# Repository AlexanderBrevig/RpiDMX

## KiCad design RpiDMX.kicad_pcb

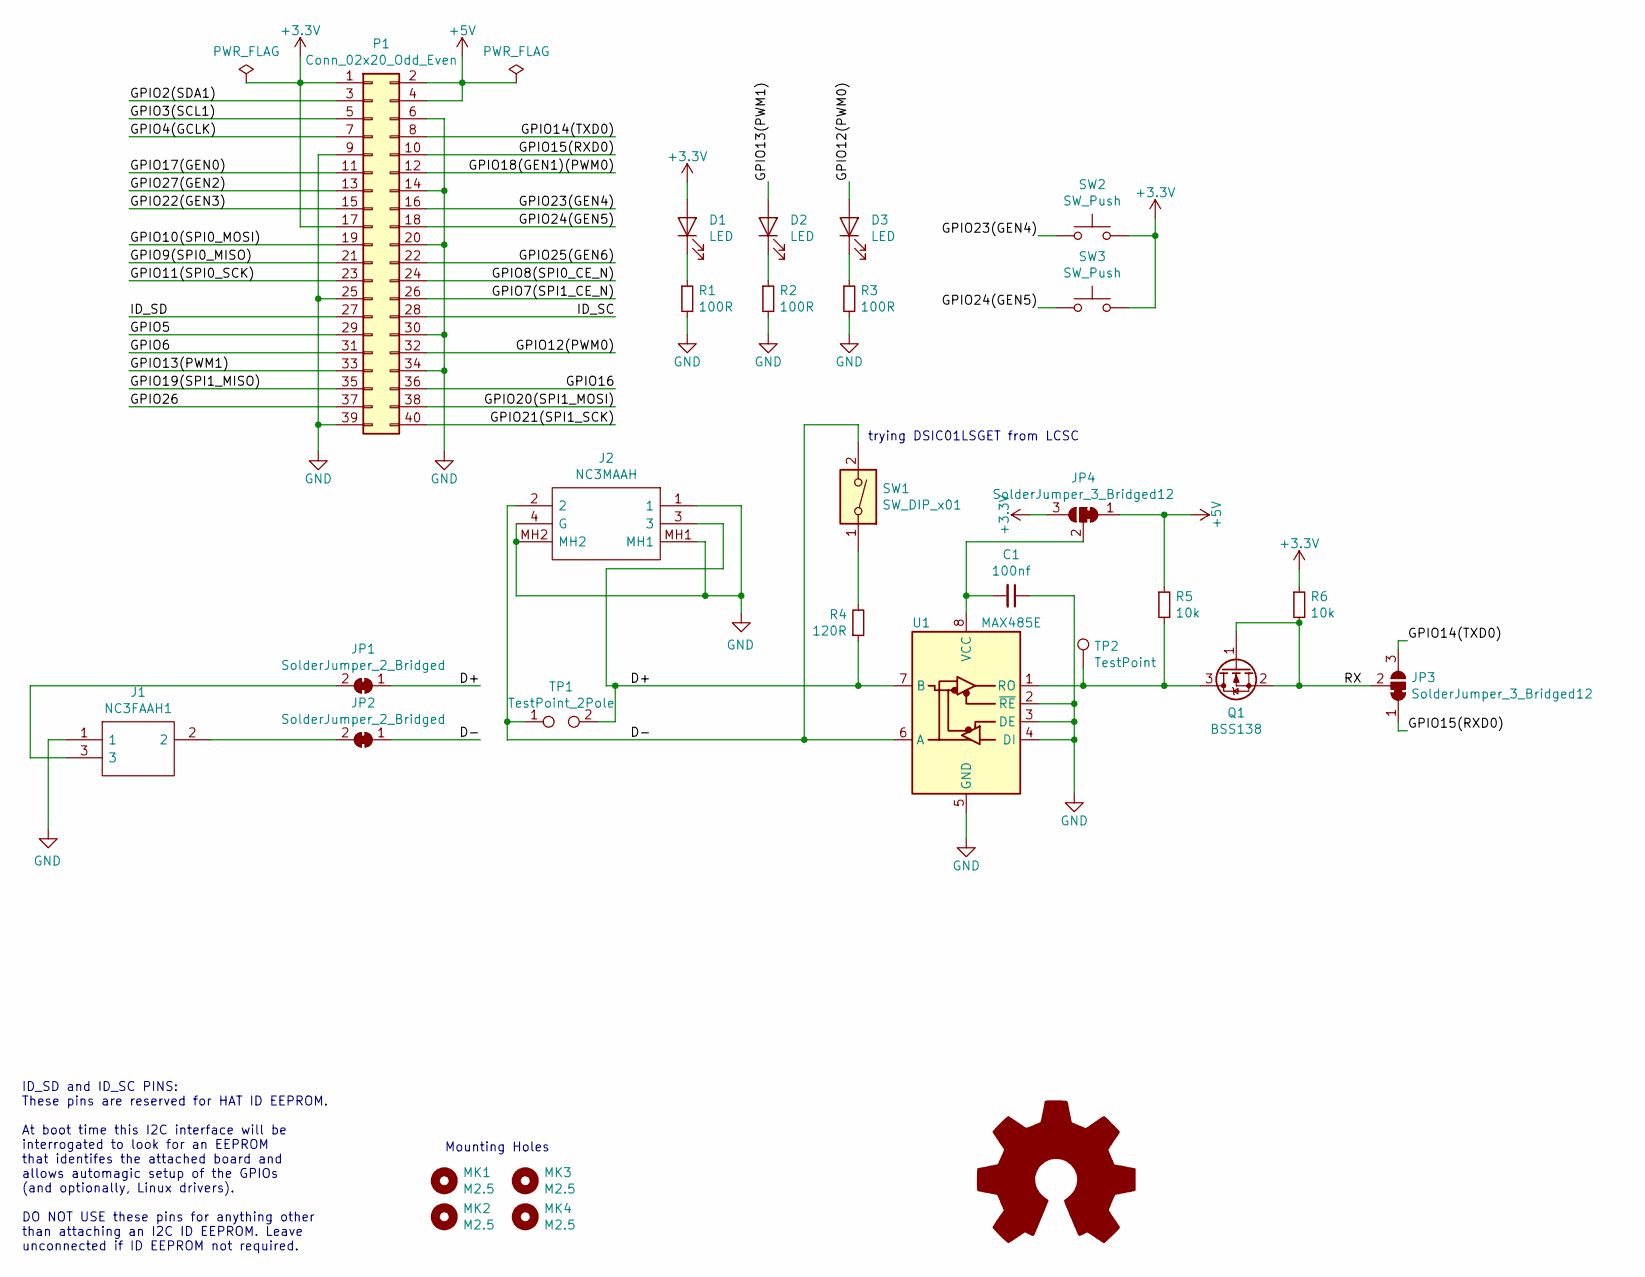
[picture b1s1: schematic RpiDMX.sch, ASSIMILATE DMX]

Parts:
C1: 100nf; C_0805_2012Metric_Pad1.15x1.40mm_HandSolder
D1, D2, D3: LED; LED_0805_2012Metric_Pad1.15x1.40mm_HandSolder
J1: NC3FAAH1; Mouser Part Number 568-NC3FAAH-1
J2: NC3MAAH; Mouser Part Number 568-NC3MAAH
JP1, JP2: SolderJumper_2_Bridged; SolderJumper-2_P1.3mm_Bridged_RoundedPad1.0x1.5mm
JP3, JP4: SolderJumper_3_Bridged12; SolderJumper-3_P1.3mm_Bridged12_RoundedPad1.0x1.5mm_NumberL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
MK1, MK2, MK3, MK4: M2.5; MountingHole_2.7mm_M2.5
P1: Conn_02x20_Odd_Even; PinSocket_2x20_P2.54mm_Vertical
Q1: BSS138; SOT-23
R1, R2, R3: 100R; R_0805_2012Metric_Pad1.15x1.40mm_HandSolder
R4: 120R; R_0805_2012Metric_Pad1.15x1.40mm_HandSolder
R5, R6: 10k; R_0805_2012Metric_Pad1.15x1.40mm_HandSolder
SW1: SW_DIP_x01; SW_DIP_SPSTx01_Slide_Omron_A6S-110x_W8.9mm_P2.54mm
SW2, SW3: SW_Push; SW_SPST_B3U-1000P
TP1: TestPoint_2Pole; TestPoint_2Pads_Pitch2.54mm_Drill0.8mm
TP2: TestPoint; TestPoint_THTPad_D1.5mm_Drill0.7mm
U1: MAX485E; SOIC-8_3.9x4.9mm_P1.27mm

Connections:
+3V3: D1.2 (A), JP4.3 (B), P1.1, P1.17, R6.1, SW2.2, SW3.2
+5V: JP4.1 (A), P1.2, P1.4, R5.1
/D+: J2.3, JP1.1 (A), R4.1, TP1.2, U1.7 (B)
/D-: J2.2, JP2.1 (A), SW1.2, TP1.1, U1.6 (A)
/GPIO2(SDA1): P1.3
/GPIO3(SCL1): P1.5
/GPIO4(GCLK): P1.7
/GPIO5: P1.29
/GPIO6: P1.31
/GPIO7(SPI1_CE_N): P1.26
/GPIO8(SPI0_CE_N): P1.24
/GPIO9(SPI0_MISO): P1.21
/GPIO10(SPI0_MOSI): P1.19
/GPIO11(SPI0_SCK): P1.23
/GPIO12(PWM0): D3.2 (A), P1.32
/GPIO13(PWM1): D2.2 (A), P1.33
/GPIO14(TXD0): JP3.3 (B), P1.8
/GPIO15(RXD0): JP3.1 (A), P1.10
/GPIO16: P1.36
/GPIO17(GEN0): P1.11
/GPIO18(GEN1)(PWM0): P1.12
/GPIO19(SPI1_MISO): P1.35
/GPIO20(SPI1_MOSI): P1.38
/GPIO21(SPI1_SCK): P1.40
/GPIO22(GEN3): P1.15
/GPIO23(GEN4): P1.16, SW2.1
/GPIO24(GEN5): P1.18, SW3.1
/GPIO25(GEN6): P1.22
/GPIO26: P1.37
/GPIO27(GEN2): P1.13
/ID_SC: P1.28
/ID_SD: P1.27
/RX: JP3.2 (C), Q1.1 (G), Q1.2 (S), R6.2
GND: C1.1, J1.1, J2.1, J2.4 (G), J2.MH1, J2.MH2, P1.6, P1.9, P1.14, P1.20, P1.25, P1.30, P1.34, P1.39, R1.2, R2.2, R3.2, U1.2 (~RE), U1.3 (DE), U1.4 (DI), U1.5 (GND)
unnamed: C1.2, JP4.2 (C), U1.8 (VCC)
unnamed: D1.1 (K), R1.1
unnamed: D2.1 (K), R2.1
unnamed: D3.1 (K), R3.1
unnamed: J1.2, JP2.2 (B)
unnamed: J1.3, JP1.2 (B)
unnamed: Q1.3 (D), R5.2, TP2.1, U1.1 (RO)
unnamed: R4.2, SW1.1

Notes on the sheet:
ID_SD and ID_SC PINS: These pins are reserved for HAT ID EEPROM. At boot time this I2C interface will be interrogated to look for an EEPROM that identifes the attached board and allows automagic setup of the GPIOs (and optionally, Linux drivers). DO NOT USE these pins for anything other than attach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
Mounting Holes
trying DSIC01LSGET from LCSC

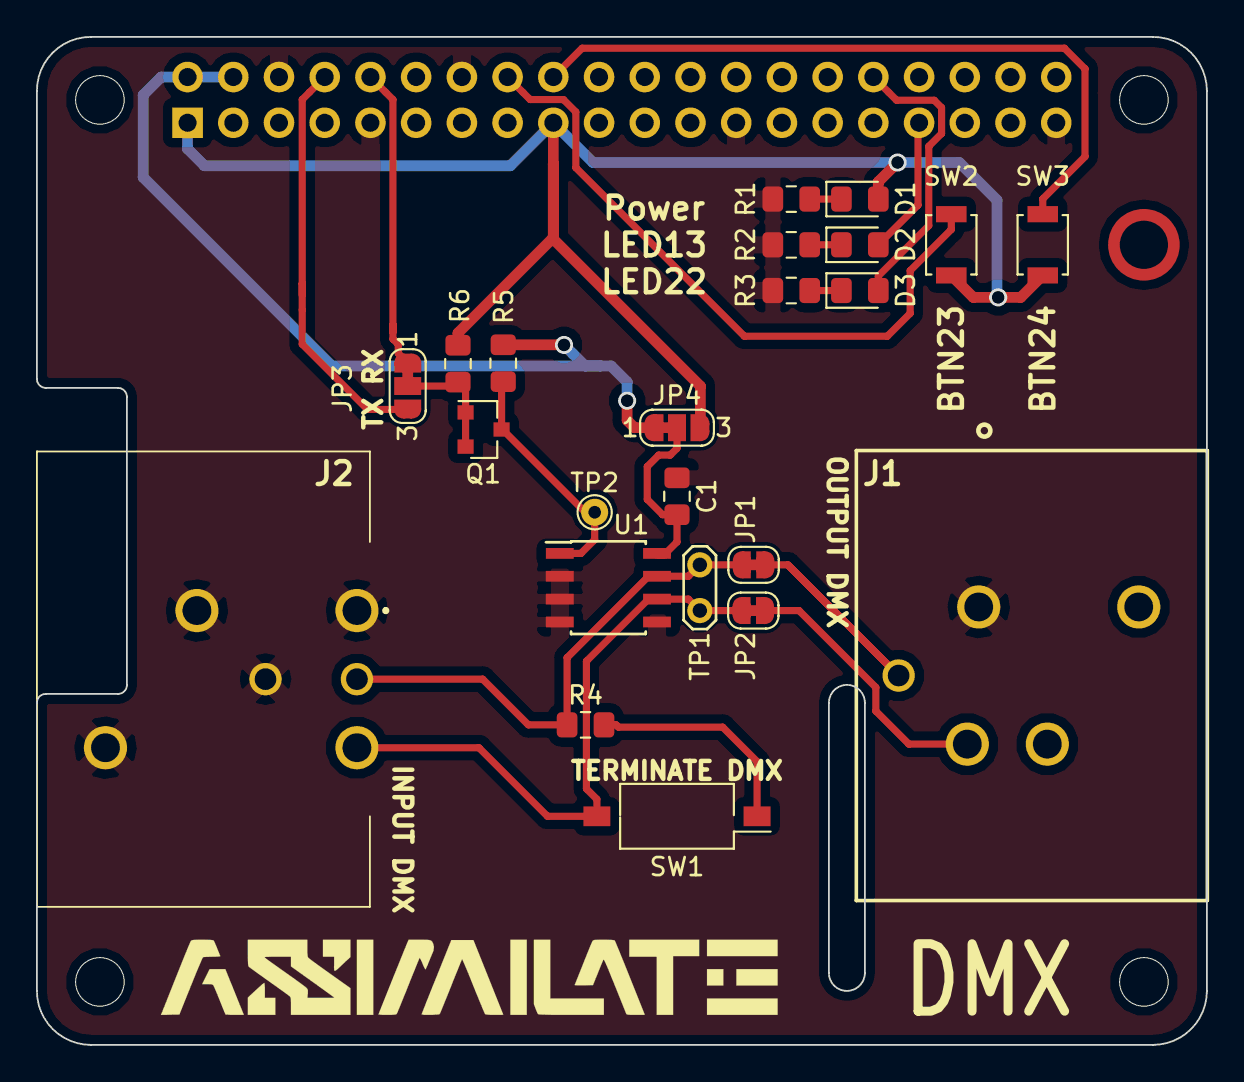
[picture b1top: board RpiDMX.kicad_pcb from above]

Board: 2 copper layers, 65.0 x 56.0 mm, 28 parts (1 on the bottom side), 20 nets.
